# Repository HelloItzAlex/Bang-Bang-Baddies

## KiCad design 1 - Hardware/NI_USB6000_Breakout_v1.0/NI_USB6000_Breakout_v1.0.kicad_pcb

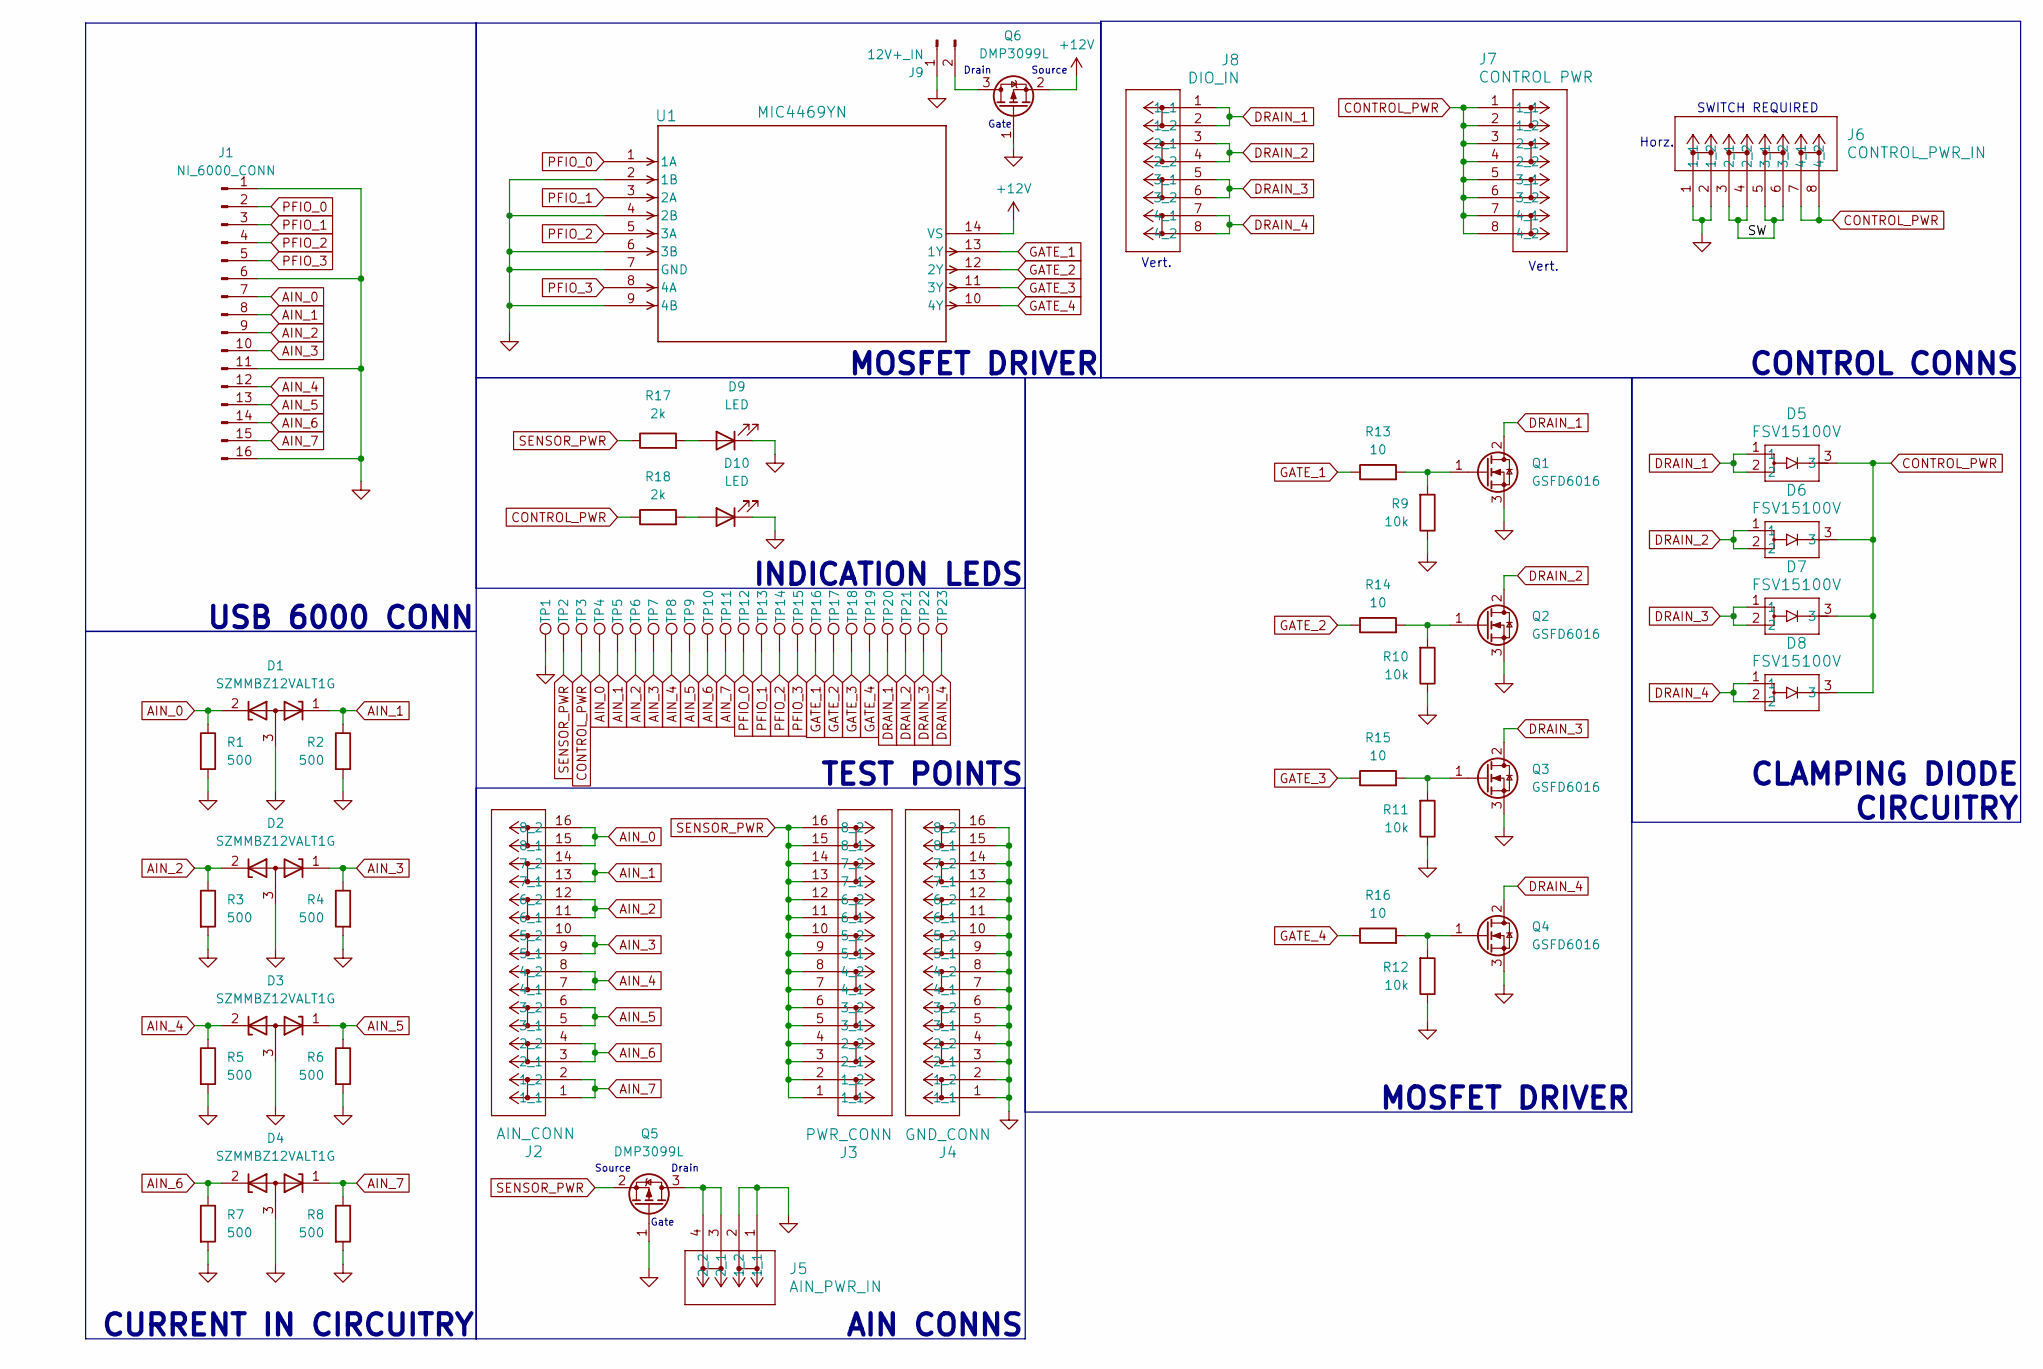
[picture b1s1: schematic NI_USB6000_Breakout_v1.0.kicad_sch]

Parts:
D1, D2, D3, D4: SZMMBZ12VALT1G; SOT-23-3
D5, D6, D7, D8: FSV15100V; TO-277-3LD_ONS
D9, D10: LED; LED_1206_3216Metric
J1: NI_6000_CONN; 3.5mmPitch01x16
J2: AIN_CONN; CONN8_2601-3108_WAG
J3: PWR_CONN; CONN8_2601-3108_WAG
J4: GND_CONN; CONN8_2601-3108_WAG
J5: AIN_PWR_IN; CONN2_2601-1102_WAG
J6: CONTROL_PWR_IN; CONN4_2601-1104_WAG
J7: CONTROL PWR; CONN4_2601-3104_WAG
J8: DIO_IN; CONN4_2601-3104_WAG
J9: 12V+_IN; PinHeader_1x02_P2.54mm_Vertical
Q1, Q2, Q3, Q4: GSFD6016; TO-252-2
Q5, Q6: DMP3099L; SOT-23-3
R1, R2, R3, R4, R5, R6, R7, R8: 500; R_0603_1608Metric
R9, R10, R11, R12: 10k; R_1206_3216Metric
R13, R14, R15, R16: 10; R_1206_3216Metric
R17, R18: 2k; R_1206_3216Metric
TP1, TP2, TP3, TP4, TP5, TP6, TP7, TP8, TP9, TP10, TP11, TP12, TP13, TP14, TP15, TP16, TP17, TP18, TP19, TP20, TP21, TP22, TP23: TestPoint; TestPoint_THTPad_D2.0mm_Drill1.0mm
U1: MIC4469YN; PDIP-14_MCL

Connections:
+12V: Q6.2 (S), U1.14 (VS)
/SW: J6.3 (2_1), J6.4 (2_2), J6.5 (3_1), J6.6 (3_2)
AIN_0: D1.2 (K), J1.7, J2.15 (8_1), J2.16 (8_2), R1.1, TP4.1
AIN_1: D1.1 (K), J1.8, J2.13 (7_1), J2.14 (7_2), R2.1, TP5.1
AIN_2: D2.2 (K), J1.9, J2.11 (6_1), J2.12 (6_2), R3.1, TP6.1
AIN_3: D2.1 (K), J1.10, J2.9 (5_1), J2.10 (5_2), R4.1, TP7.1
AIN_4: D3.2 (K), J1.12, J2.7 (4_1), J2.8 (4_2), R5.1, TP8.1
AIN_5: D3.1 (K), J1.13, J2.5 (3_1), J2.6 (3_2), R6.1, TP9.1
AIN_6: D4.2 (K), J1.14, J2.3 (2_1), J2.4 (2_2), R7.1, TP10.1
AIN_7: D4.1 (K), J1.15, J2.1 (1_1), J2.2 (1_2), R8.1, TP11.1
CONTROL_PWR: D5.3, D6.3, D7.3, D8.3, J6.7 (4_1), J6.8 (4_2), J7.1 (1_1), J7.2 (1_2), J7.3 (2_1), J7.4 (2_2), J7.5 (3_1), J7.6 (3_2), J7.7 (4_1), J7.8 (4_2), R18.1, TP3.1
DRAIN_1: D5.1, D5.2, J8.1 (1_1), J8.2 (1_2), Q1.2 (D), TP20.1
DRAIN_2: D6.1, D6.2, J8.3 (2_1), J8.4 (2_2), Q2.2 (D), TP21.1
DRAIN_3: D7.1, D7.2, J8.5 (3_1), J8.6 (3_2), Q3.2 (D), TP22.1
DRAIN_4: D8.1, D8.2, J8.7 (4_1), J8.8 (4_2), Q4.2 (D), TP23.1
GATE_1: R13.1, TP16.1, U1.13 (1Y)
GATE_2: R14.1, TP17.1, U1.12 (2Y)
GATE_3: R15.1, TP18.1, U1.11 (3Y)
GATE_4: R16.1, TP19.1, U1.10 (4Y)
GND: D1.3 (A), D2.3 (A), D3.3 (A), D4.3 (A), D9.1 (K), D10.1 (K), J1.1, J1.6, J1.11, J1.16, J4.1 (1_1), J4.2 (1_2), J4.3 (2_1), J4.4 (2_2), J4.5 (3_1), J4.6 (3_2), J4.7 (4_1), J4.8 (4_2), J4.9 (5_1), J4.10 (5_2), J4.11 (6_1), J4.12 (6_2), J4.13 (7_1), J4.14 (7_2), J4.15 (8_1), J4.16 (8_2), J5.1 (1_1), J5.2 (1_2), J6.1 (1_1), J6.2 (1_2), J9.1, Q1.3 (S), Q2.3 (S), Q3.3 (S), Q4.3 (S), Q5.1 (G), Q6.1 (G), R1.2, R2.2, R3.2, R4.2, R5.2, R6.2, R7.2, R8.2, R9.1, R10.1, R11.1, R12.1, TP1.1, U1.2 (1B), U1.4 (2B), U1.6 (3B), U1.7 (GND), U1.9 (4B)
unnamed: D9.2 (A), R17.2
unnamed: D10.2 (A), R18.2
unnamed: J5.3 (2_1), J5.4 (2_2), Q5.3 (D)
unnamed: J9.2, Q6.3 (D)
unnamed: Q1.1 (G), R9.2, R13.2
unnamed: Q2.1 (G), R10.2, R14.2
unnamed: Q3.1 (G), R11.2, R15.2
unnamed: Q4.1 (G), R12.2, R16.2
PFIO_0: J1.2, TP12.1, U1.1 (1A)
PFIO_1: J1.3, TP13.1, U1.3 (2A)
PFIO_2: J1.4, TP14.1, U1.5 (3A)
PFIO_3: J1.5, TP15.1, U1.8 (4A)
SENSOR_PWR: J3.1 (1_1), J3.2 (1_2), J3.3 (2_1), J3.4 (2_2), J3.5 (3_1), J3.6 (3_2), J3.7 (4_1), J3.8 (4_2), J3.9 (5_1), J3.10 (5_2), J3.11 (6_1), J3.12 (6_2), J3.13 (7_1), J3.14 (7_2), J3.15 (8_1), J3.16 (8_2), Q5.2 (S), R17.1, TP2.1

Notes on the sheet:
CURRENT IN CIRCUITRY
MOSFET DRIVER
CONTROL CONNS
Gate
Vert.
Source
SWITCH REQUIRED
Drain
Horz.
USB 6000 CONN
INDICATION LEDS
CLAMPING DIODE CIRCUITRY
TEST POINTS
AIN CONNS

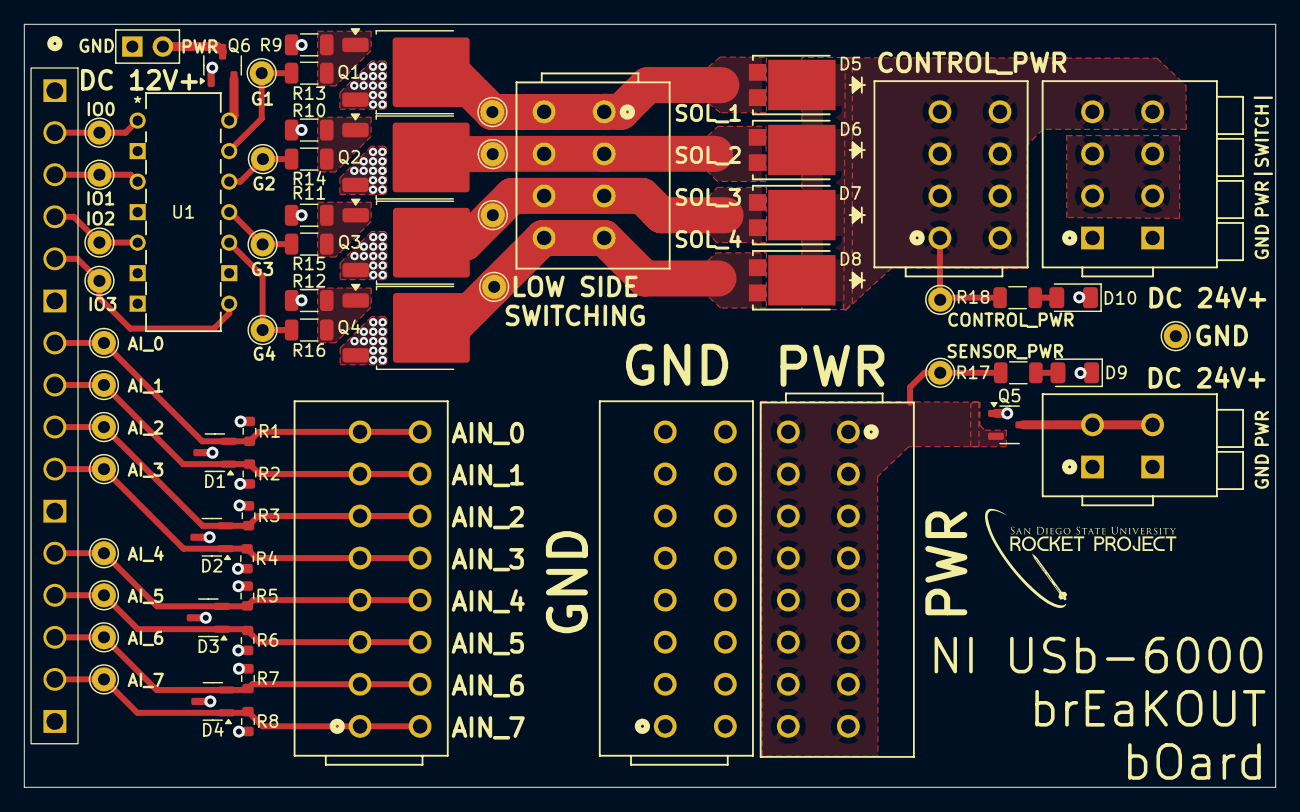
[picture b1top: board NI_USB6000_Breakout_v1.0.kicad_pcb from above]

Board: 2 copper layers, 104.1 x 63.5 mm, 67 parts (0 on the bottom side), 33 nets.

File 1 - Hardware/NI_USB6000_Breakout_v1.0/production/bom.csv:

Designator,Footprint,Quantity,Value,LCSC Part #
"D1, D2, D3, D4",SOT-23-3,4,SZMMBZ12VALT1G,
"D10, D9",1206,2,LED,
"D5, D6, D7, D8",TO-277-3LD_ONS,4,FSV15100V,
J1,3.5mmPitch01x16,1,NI_6000_CONN,
J2,CONN8_2601-3108_WAG,1,AIN_CONN,
J3,CONN8_2601-3108_WAG,1,PWR_CONN,
J4,CONN8_2601-3108_WAG,1,GND_CONN,
J5,CONN2_2601-1102_WAG,1,AIN_PWR_IN,
J6,CONN4_2601-1104_WAG,1,CONTROL_PWR_IN,
J7,CONN4_2601-3104_WAG,1,CONTROL PWR,
J8,CONN4_2601-3104_WAG,1,DIO_IN,
J9,PinHeader_1x02_P2.54mm_Vertical,1,12V+_IN,
"Q1, Q2, Q3, Q4",TO-252-2,4,GSFD6016,
"Q5, Q6",SOT-23-3,2,DMP3099L,
"R1, R2, R3, R4, R5, R6, R7, R8",0603,8,500,
"R10, R11, R12, R9",1206,4,10k,
"R13, R14, R15, R16",1206,4,10,
"R17, R18",1206,2,2k,
"TP1, TP10, TP11, TP12, TP13, TP14, TP15, TP16, TP17, TP18, TP19, TP2, TP20, TP21, TP22, TP23, TP3, TP4, TP5, TP6, TP7, TP8, TP9",TestPoint_THTPad_D2.0mm_Drill1.0mm,23,TestPoint,
U1,PDIP-14_MCL,1,MIC4469YN,

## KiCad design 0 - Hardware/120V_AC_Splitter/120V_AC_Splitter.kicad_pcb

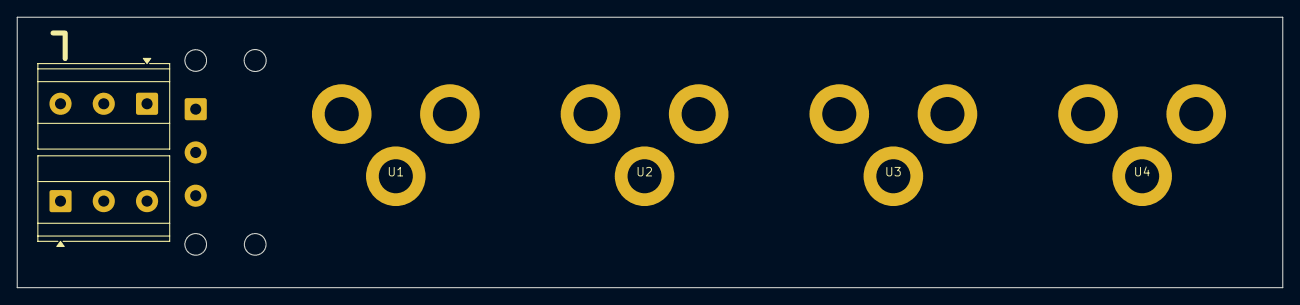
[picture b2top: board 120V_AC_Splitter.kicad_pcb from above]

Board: 2 copper layers, 148.6 x 31.8 mm, 7 parts (0 on the bottom side), 4 nets, no tracks yet.

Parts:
J1: IN; TerminalBlock_Phoenix_MKDS-1,5-3-5.08_1x03_P5.08mm_Horizont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
J2: OUT; TerminalBlock_Phoenix_MKDS-1,5-3-5.08_1x03_P5.08mm_Horizont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
J3: SWITCH; TerminalBlock_Phoenix_MKDS-1,5-3-5.08_1x03_P5.08mm_Horizont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
U1, U2, U3, U4: Untitled

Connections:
Earth: J1.2, J2.2, U1.3 (EARTH_GND), U2.3 (EARTH_GND), U3.3 (EARTH_GND), U4.3 (EARTH_GND)
LIVE: J1.3, J2.1, J3.3
NEUTRAL: J1.1, J2.3, J3.1, U1.1 (NEUTRAL), U2.1 (NEUTRAL), U3.1 (NEUTRAL), U4.1 (NEUTRAL)
SWITCH: J3.2, U1.2 (LIVE), U2.2 (LIVE), U3.2 (LIVE), U4.2 (LIVE)

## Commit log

2026-02-02 Moved USB 6000 breakout in
2026-02-02 Extra files
2026-02-04 Work
2026-02-05 USB 6000 Breakout work
2026-02-05 USB 6000 KiCAD Work
2026-02-10 USB 6000 Breakout Board and code shuffling
2026-02-12 Added testing folder
2026-02-12 Pastes
2026-02-12 Synnax Example Copy
2026-02-12 Remove AO
2026-02-19 Stuff
2026-02-26 Update SynnaxAIDisplay.py
    Annotation Updates
2026-06-23 Splitting changes
